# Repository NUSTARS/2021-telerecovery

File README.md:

# Recovery Systems Telemetry Module (SkyNet)
A Telemetry Software-Hardware Package for High Powered Rockets.

# TODO:
- [ ] Implement storing data in onboard flash memory in transmitter board
- [ ] Implement GPS reading
- [ ] Use sensor readings to determine apogee
- [ ] Move calculations to groundstation when feasilble such as altitude from pressure
- [ ] Calculate pressure with current temperature from sensor for greater accuracy
- [ ] Improvements on groundstation

## Useage

The easiest way to use the code in this repo is to download PlatformIO and use the provided platformio.ini initialization file when you create a new project. PlatformIO works great with VS code. 

Checkout the [Wiki](https://github.com/NUSTARS/2021-telerecovery/wiki/Hardware) page for more information. 

### Google Drive
Here is a [Google Drive link](https://drive.google.com/drive/u/1/folders/1rWdLhBEQf0NXYTq_rxv_L2-M3DT5xfJa) for anything else we may not want to put on GitHub like pictures, videos, test results, etc.

## Initial Objectives:
- Under $200 total 
- 2 mile range to be safe
  - Assuming typical NSL flight profile, apogee is typically between 4000-6000ft 
- Small form factor
  - Do not want to take up too much space in the rocket 
- Detect separation of launch vehicle
- Collect as much data as possible; acceleration, gyro, pressure, temperature
- Protected from black powder residue
- Remember to consider the fact that carbon fiber is RF opaque
- Cross-platform desktop GUI application for displaying sensor data in a nice way

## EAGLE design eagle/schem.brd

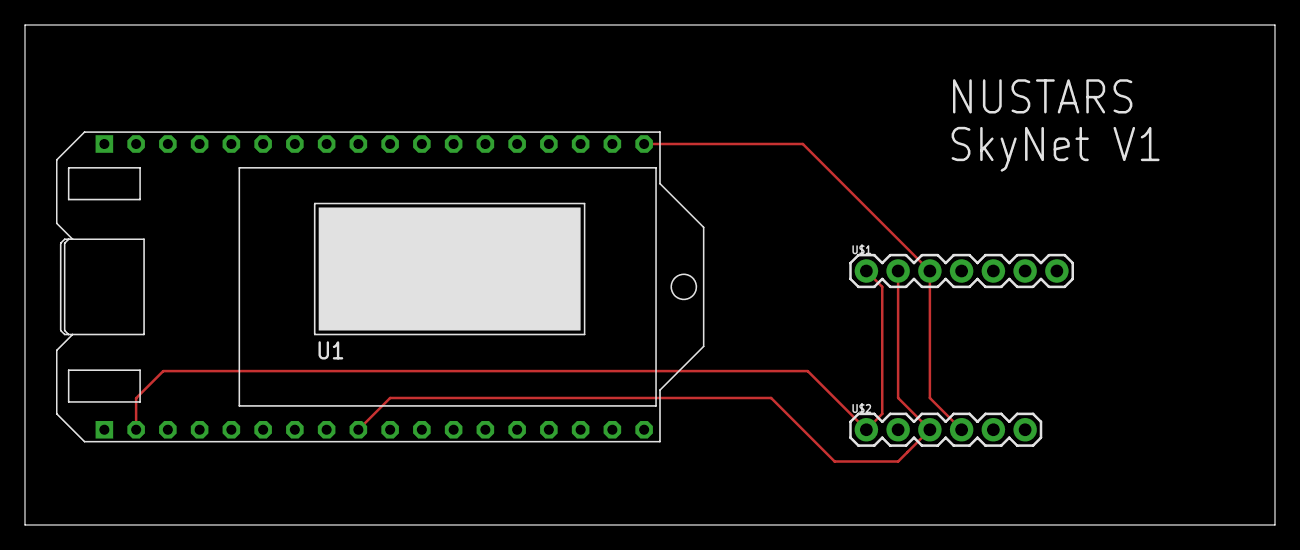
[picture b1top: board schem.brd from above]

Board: 2 copper layers, 100.0 x 40.0 mm, 3 parts (0 on the bottom side), 4 nets.

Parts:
U1: WIFI-LORA-32-V2; 2.54MM_2X18
U$1: BERRYIMU; 1X07
U$2: VL53L0X; 1X06

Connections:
+5V: U1.P$2, U$1.1, U$2.1
GND: U1.P$1, U1.P$36, U$1.4, U$2.2
SCL: U1.P$9, U$1.2, U$2.3
SDA: U1.P$19, U$1.3, U$2.4

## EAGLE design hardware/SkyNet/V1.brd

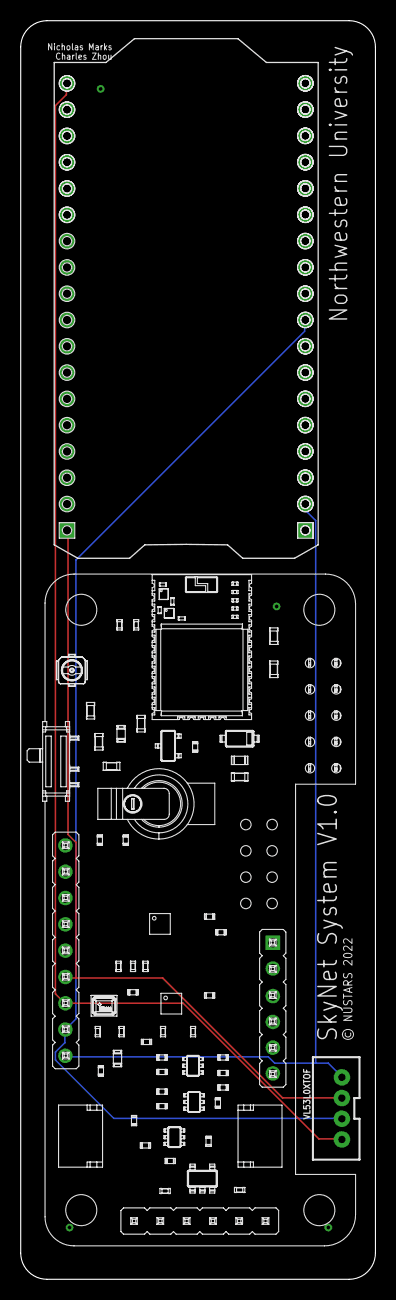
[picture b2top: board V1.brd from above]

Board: 2 copper layers, 34.3 x 121.6 mm, 3 parts (0 on the bottom side), 4 nets.

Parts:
BERRYGPSIMU1: BERRYGPSV4
LORA1: WIFI-LORA32-V2
VL53L0XTOF: JST-4-PTH-VERT

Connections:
5V: BERRYGPSIMU1.5V, LORA1.5V, VL53L0XTOF.4
GND: BERRYGPSIMU1.GND, LORA1.GND, VL53L0XTOF.3
SCL: BERRYGPSIMU1.SCL5V, LORA1.SCL, VL53L0XTOF.2
SDA: BERRYGPSIMU1.SDA5V, LORA1.SDA, VL53L0XTOF.1

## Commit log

2021-06-27 add .gitignore
2021-06-27 add proposal
2021-07-18 create platformio project
2021-07-18 add ChipID
2021-07-18 add OLED_LoRa_Sender example code
2021-07-19 updated with V2 version
2021-07-19 add LoRa sender example code
2021-07-19 create ground_station platformio project, add example code
2021-07-19 add chipid.cpp
2021-07-19 example code works
2021-07-19 update gitignore
2021-07-19 revert gitignore
2021-07-19 add pinout pdf
2021-07-20 rename stuff
2021-07-20 rename
2021-07-21 ToF sensor test works
2021-07-21 ToF test lib works, init function doesn't though
2021-07-21 test working
2021-07-21 move ToF lib test into project
2021-07-22 works, cannot use ToF together with OLED
2021-07-22 ToF data successfuly sends with LoRa
2021-07-22 update main
2021-07-23 create OLED lib
2021-07-23 updare
2021-07-24 refactor into multiple cpp and h files
2021-07-25 addded python object to json test
2021-07-29 Added SkyNet groundstation software
    Initial version
2021-07-29 add serial printing, other updates
2021-07-29 add serial printing
2021-07-29 remove unneccesary python code
2021-07-29 reorganize into lib folder
2021-07-29 reorganize stuff in lib folder
2021-08-03 Reduce css size
2021-08-07 Update dependencies to new versions
2021-09-06 add BerryIMU sample code to test dir
2021-09-13 BerryIMU test works I think
2021-09-13 add BerryIMU to lib folder
2021-09-13 add baud to platformio.ini
2021-09-14 renamed 'sender' dir to 'transmitter'
2021-09-14 rename dir 'sender' to 'transmitter'
2021-09-15 add BMP388 header
2021-09-15 removed irrelevant stuff for v1 and v2 versions
2021-09-15 reformat
2021-09-15 remove old tests, add adafruit BMP388 library
2021-09-16 close but no cigar on bmp388
2021-09-16 all sensors working
2021-09-16 remove gitmodule
2021-09-16 add eagle folder
2021-09-16 package data into array first, then print, and other updates
2021-09-16 updates to printing
2021-09-16 removed delay that was slowing down transmission
2021-09-16 working ok, about 3s/packet recvd
2021-09-17 increase buffer size
2021-09-17 added gyro and CF angles to data, transmission is also faster now
2021-09-17 refactoring
2021-09-18 make new folders and reorganize
2021-09-18 add dimensions
2021-09-18 add eagle files
2021-09-18 fix eagle files
2021-10-12 Bump electron from 13.1.8 to 13.3.0 in /groundstation/SkyNet
    Bumps [electron](https://github.com/electron/electron) from 13.1.8 to 13.3.0.
    - [Release notes](https://github.com/electron/electron/releases)
    - [Changelog](https://github.com/electron/electron/blob/main/docs/breaking-changes.md)
    - [Commits](https://github.com/electron/electron/compare/v13.1.8...v13.3.0)
    ---
    updated-dependencies:
2021-12-05 Update platformio.ini
    Includes missing dependency
2021-12-18 add comments, increase buffer size to prevent overflow
2021-12-18 Update dependencies
2021-12-18 Serialport has compatibility issues with electron version>13
2021-12-21 add submodule Adafruit_AHRS
2021-12-21 move Adafruit_AHRS
2021-12-21 save
2021-12-25 compiles but doesn't find sensor
2021-12-25 setting up
2021-12-25 move stuff to lib
2021-12-25 IMU data output looks good!
2021-12-25 IMU is working I think
2021-12-25 moved stuff to test
2021-12-25 moved adafruit libs to platformio.ini file as links
2021-12-26 move AHRS to link in libdeps section of platformio.ini
2021-12-26 9(IMU)+4(ToF and BMP) dof sensors all output good data
2021-12-28 removed calibration stuff and added lora transmission
2021-12-28 remove unneeded /n in data buffer
2021-12-29 overhall sensor reading with new adafruit libraries
2021-12-29 remove gitmodules
2021-12-29 Removed IMU.c and IMU.cpp because they are no longer needed (I think)
2021-12-29 forgot to remove a print
2021-12-29 add python scripts for reading serial data from reciever for testing/debugging
2021-12-29 add more comments
2021-12-29 change the 20ms delay
2021-12-29 change 20ms delay, arduino delay() function is bad
2022-01-08 Update Skynet
2022-01-08 Revert "Merge branch 'main' of https://github.com/NUSTARS/2021-telerecovery"
    This reverts commit 339799553d41e9301c50609017da7b716ce3b563, reversing
    changes made to cd481ba09471f784a15fa7aeb49dcb35e36d6197.
2022-01-08 Revert "Update Skynet"
    This reverts commit cd481ba09471f784a15fa7aeb49dcb35e36d6197.
2022-01-08 Revert "Revert "Merge branch 'main' of https://github.com/NUSTARS/2021-telerecovery""
    This reverts commit 8990767382afad5a45817f910757894a7d4a18d8.
2022-01-08 First working version of SkyNet
2022-01-08 Bug fixes
    Fixed the chart starting position issue (zero)
    Fixed the serial devices update frequency (low)
2022-01-08 Display local and UTC time on the dashboard
2022-01-08 Added packages RSSI reporting and display
2022-01-08 Update logo
2022-01-11 remove linux_installer.sh, we'll do that later
2022-01-17 data buffer size of 200 bytes works, increased signal bandwith to increase speed
2022-01-17 WOW, THAT's FAST
2022-03-23 add MIT license
2022-03-23 Bump minimist from 1.2.5 to 1.2.6 in /groundstation/SkyNet
    Bumps [minimist](https://github.com/substack/minimist) from 1.2.5 to 1.2.6.
    - [Release notes](https://github.com/substack/minimist/releases)
    - [Commits](https://github.com/substack/minimist/compare/1.2.5...1.2.6)
    ---
    updated-dependencies:
    - dependency-name: minimist
2022-04-07 Bump plist from 3.0.4 to 3.0.5 in /groundstation/SkyNet
    Bumps [plist](https://github.com/TooTallNate/node-plist) from 3.0.4 to 3.0.5.
    - [Release notes](https://github.com/TooTallNate/node-plist/releases)
    - [Changelog](https://github.com/TooTallNate/plist.js/blob/master/History.md)
    - [Commits](https://github.com/TooTallNate/node-plist/commits)
    ---
    updated-dependencies:
2022-04-07 Bump electron from 13.6.3 to 13.6.6 in /groundstation/SkyNet
    Bumps [electron](https://github.com/electron/electron) from 13.6.3 to 13.6.6.
    - [Release notes](https://github.com/electron/electron/releases)
    - [Changelog](https://github.com/electron/electron/blob/main/docs/breaking-changes.md)
    - [Commits](https://github.com/electron/electron/compare/v13.6.3...v13.6.6)
    ---
    updated-dependencies:
2022-04-07 Bump simple-get from 4.0.0 to 4.0.1 in /groundstation/SkyNet
    Bumps [simple-get](https://github.com/feross/simple-get) from 4.0.0 to 4.0.1.
    - [Release notes](https://github.com/feross/simple-get/releases)
    - [Commits](https://github.com/feross/simple-get/compare/v4.0.0...v4.0.1)
    ---
    updated-dependencies:
    - dependency-name: simple-get
2022-04-19 Enable Vext
2022-05-03 Update Board Pinout PDF
2022-05-03 Correct PCB for internal LiPO
    5V bus -> 3V3
2022-06-17 Bump electron from 13.6.6 to 15.5.5 in /groundstation/SkyNet
    Bumps [electron](https://github.com/electron/electron) from 13.6.6 to 15.5.5.
    - [Release notes](https://github.com/electron/electron/releases)
    - [Changelog](https://github.com/electron/electron/blob/main/docs/breaking-changes.md)
    - [Commits](https://github.com/electron/electron/compare/v13.6.6...v15.5.5)
    ---
    updated-dependencies:
2022-10-10 update r readme
2022-10-30 Fixed BMP3XX library and bump dependencies
2022-10-30 Cleanup code
2022-10-30 modified: transmitter/include/transmitter.h modified: transmitter/platformio.ini modified: transmitter/src/main.cpp
2022-11-04 Vext, Startup status, I2C Bus
    Vext now works with battery, OLED Startup Status, New I2C Bus to avoid conflict with Vext control
2022-11-10 Bump electron from 13.6.9 to 18.3.7 in /groundstation/SkyNet
    Bumps [electron](https://github.com/electron/electron) from 13.6.9 to 18.3.7.
    - [Release notes](https://github.com/electron/electron/releases)
    - [Changelog](https://github.com/electron/electron/blob/main/docs/breaking-changes.md)
    - [Commits](https://github.com/electron/electron/compare/v13.6.9...v18.3.7)
    ---
    updated-dependencies:
2022-11-13 OLED GPS Status
    Display the current GPS status on the OLED screen
2022-11-15 V2.0 PCB
2023-01-01 Basic state machine and ack
2023-02-02 Adjust delay for LoRa commands (best effort)
2023-02-03 Bump http-cache-semantics from 4.1.0 to 4.1.1 in /groundstation/SkyNet
    Bumps [http-cache-semantics](https://github.com/kornelski/http-cache-semantics) from 4.1.0 to 4.1.1.
    - [Release notes](https://github.com/kornelski/http-cache-semantics/releases)
    - [Commits](https://github.com/kornelski/http-cache-semantics/compare/v4.1.0...v4.1.1)
    ---
    updated-dependencies:
    - dependency-name: http-cache-semantics
2023-02-05 Update LoRa_RX.cpp
    Compatible with Serial Studio
2023-04-22 Bump minimatch and @electron/universal in /groundstation/SkyNet
    Bumps [minimatch](https://github.com/isaacs/minimatch) and [@electron/universal](https://github.com/electron/universal). These dependencies needed to be updated together.
    Updates `minimatch` from 3.0.4 to 3.1.2
    - [Release notes](https://github.com/isaacs/minimatch/releases)
    - [Changelog](https://github.com/isaacs/minimatch/blob/main/changelog.md)
    - [Commits](https://github.com/isaacs/minimatch/compare/v3.0.4...v3.1.2)
    Updates `@electron/universal` from 1.3.1 to 1.3.4
2023-04-22 Bump got, electron and electron-packager in /groundstation/SkyNet
    Bumps [got](https://github.com/sindresorhus/got) to 11.8.6 and updates ancestor dependencies [got](https://github.com/sindresorhus/got), [electron](https://github.com/electron/electron) and [electron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
    Updates `got` from 9.6.0 to 11.8.6
    - [Release notes](https://github.com/sindresorhus/got/releases)
    - [Commits](https://github.com/sindresorhus/got/compare/v9.6.0...v11.8.6)
    Updates `electron` from 13.6.9 to 24.1.2
    - [Release notes](https://github.com/electron/electron/releases)

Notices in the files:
hardware/SkyNet/V1.brd:
© NUSTARS 2022
parts and their libraries:
SparkFun-Connectors: Licensing: Creative Commons ShareAlike 4.0 International - https://creativecommons.org/licenses/by-sa/4.0
